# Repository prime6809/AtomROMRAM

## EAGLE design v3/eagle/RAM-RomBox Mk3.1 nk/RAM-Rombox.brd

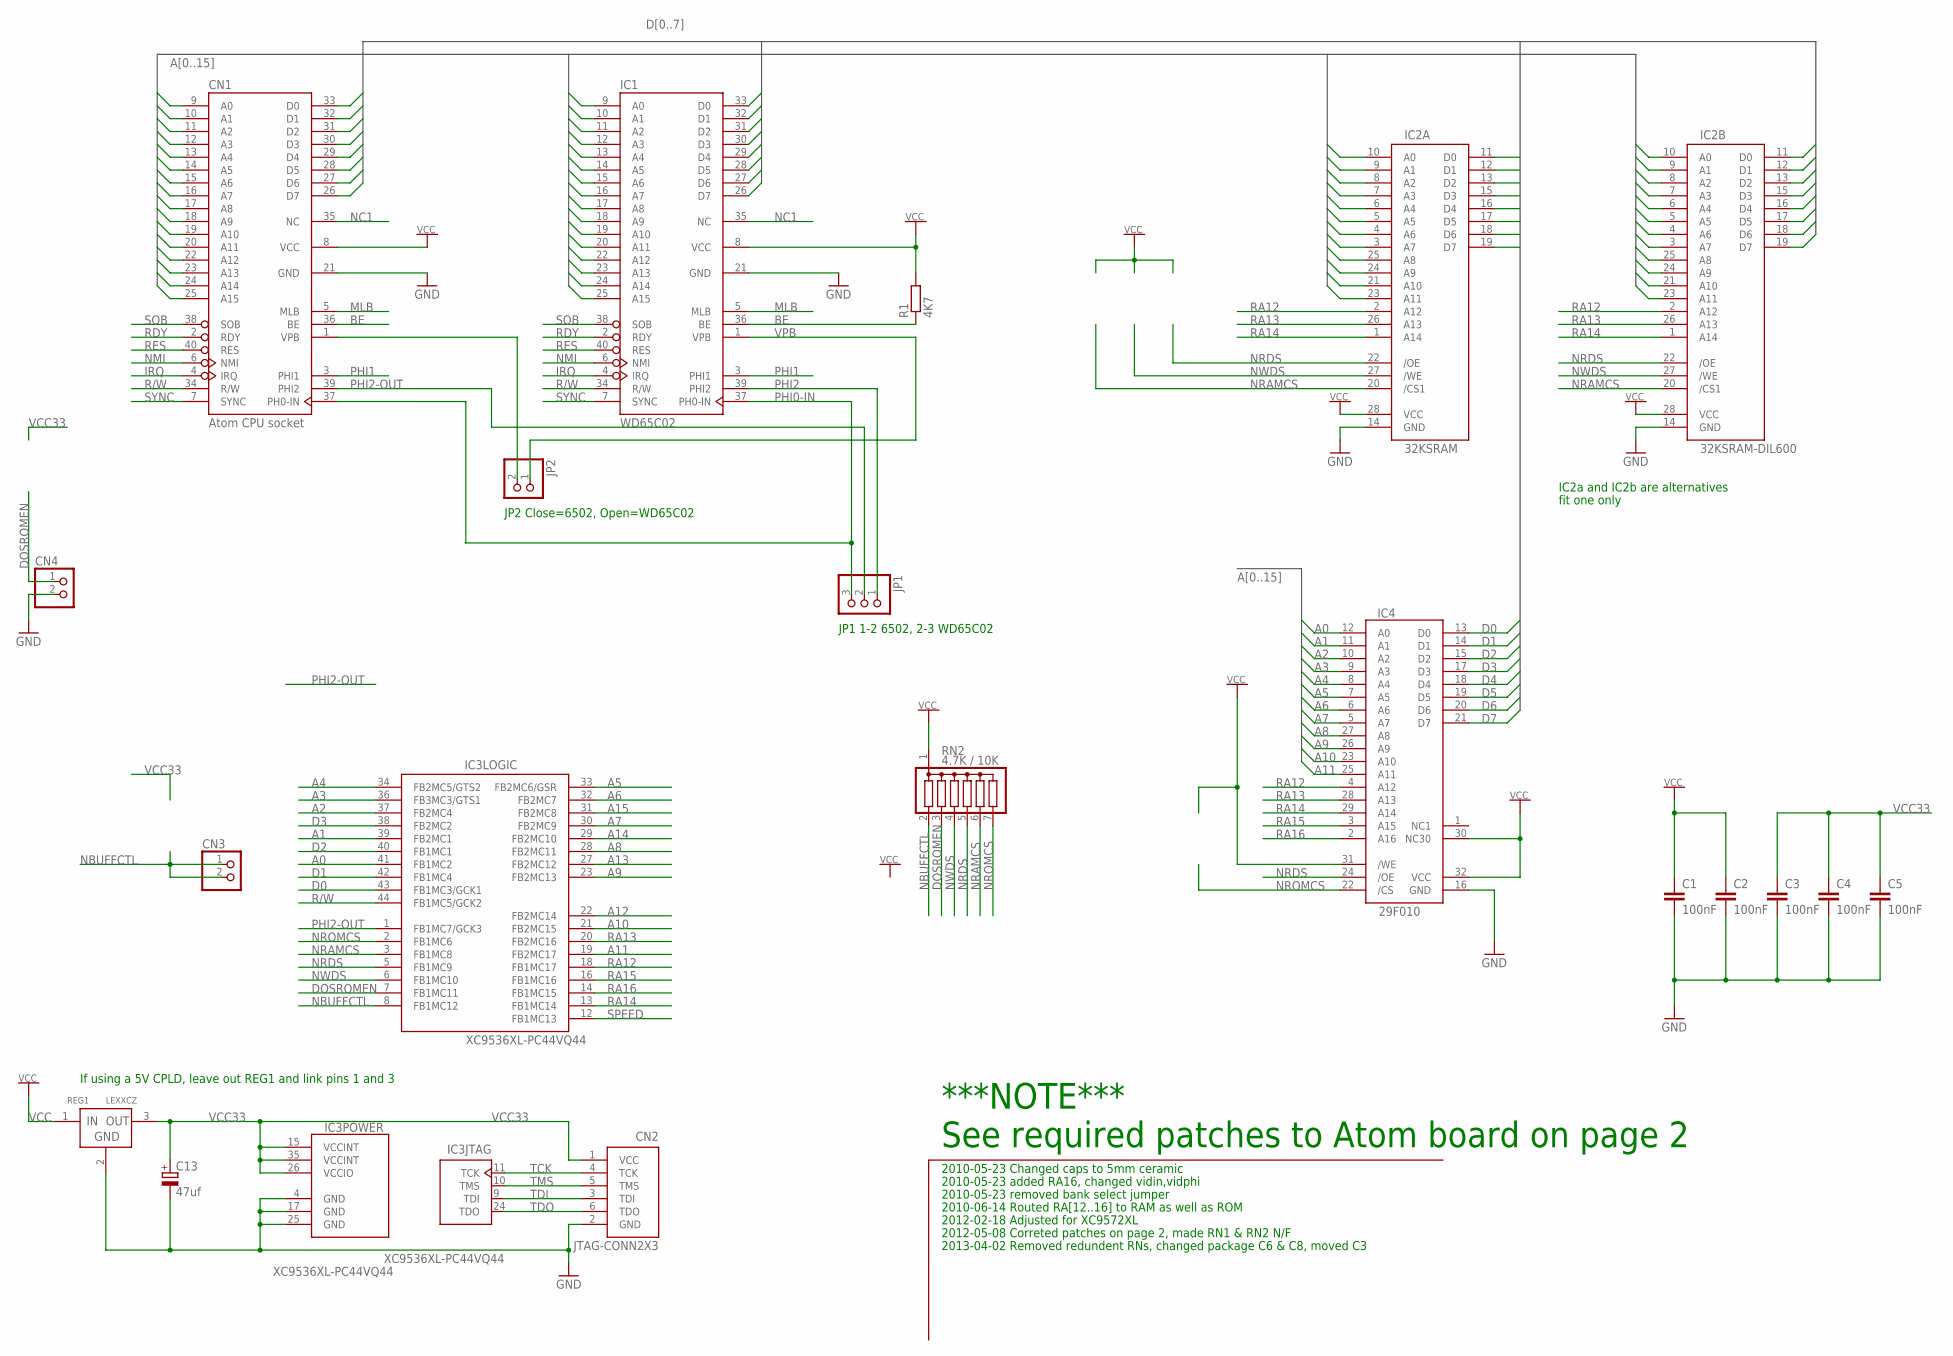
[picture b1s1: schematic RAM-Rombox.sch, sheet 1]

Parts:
C1, C2, C3: 100nF; C025-025X050
C4, C5: 100nF; C050-024X044
C13: 47uf; TAP5-45
CN1: Atom CPU socket; DIL40
CN2: JTAG-CONN2X3; 2X3
CN3, CN4: PINHD-1X2; 1X02
IC1: WD65C02; DIL40
IC2A: 32KSRAM; DIL28-3
IC2B: 32KSRAM-DIL600; DIL28-6
IC3: XC9536XL-PC44VQ44; SQFP-S-10X10-44
IC4: 29F010; DIL32
JP1: PINHD-1X3; 1X03
JP2: PINHD-1X2; 1X02
R1: 4K7; 0207/10
REG1: LEXXCZ; TO92-
RN2: 4.7K / 10K; SIL7

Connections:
A0: CN1.9 (A0), IC1.9 (A0), IC2A.10 (A0), IC2B.10 (A0), IC3.41 (FB1MC2), IC4.12 (A0)
A1: CN1.10 (A1), IC1.10 (A1), IC2A.9 (A1), IC2B.9 (A1), IC3.39 (FB2MC1), IC4.11 (A1)
A2: CN1.11 (A2), IC1.11 (A2), IC2A.8 (A2), IC2B.8 (A2), IC3.37 (FB2MC4), IC4.10 (A2)
A3: CN1.12 (A3), IC1.12 (A3), IC2A.7 (A3), IC2B.7 (A3), IC3.36 (FB3MC3/GTS1), IC4.9 (A3)
A4: CN1.13 (A4), IC1.13 (A4), IC2A.6 (A4), IC2B.6 (A4), IC3.34 (FB2MC5/GTS2), IC4.8 (A4)
A5: CN1.14 (A5), IC1.14 (A5), IC2A.5 (A5), IC2B.5 (A5), IC3.33 (FB2MC6/GSR), IC4.7 (A5)
A6: CN1.15 (A6), IC1.15 (A6), IC2A.4 (A6), IC2B.4 (A6), IC3.32 (FB2MC7), IC4.6 (A6)
A7: CN1.16 (A7), IC1.16 (A7), IC2A.3 (A7), IC2B.3 (A7), IC3.30 (FB2MC9), IC4.5 (A7)
A8: CN1.17 (A8), IC1.17 (A8), IC2A.25 (A8), IC2B.25 (A8), IC3.28 (FB2MC11), IC4.27 (A8)
A9: CN1.18 (A9), IC1.18 (A9), IC2A.24 (A9), IC2B.24 (A9), IC3.23 (FB2MC13), IC4.26 (A9)
A10: CN1.19 (A10), IC1.19 (A10), IC2A.21 (A10), IC2B.21 (A10), IC3.21 (FB2MC15), IC4.23 (A10)
A11: CN1.20 (A11), IC1.20 (A11), IC2A.23 (A11), IC2B.23 (A11), IC3.19 (FB2MC17), IC4.25 (A11)
A12: CN1.22 (A12), IC1.22 (A12), IC3.22 (FB2MC14)
A13: CN1.23 (A13), IC1.23 (A13), IC3.27 (FB2MC12)
A14: CN1.24 (A14), IC1.24 (A14), IC3.29 (FB2MC10)
A15: CN1.25 (A15), IC1.25 (A15), IC3.31 (FB2MC8)
BE: CN1.36 (BE), IC1.36 (BE), R1.1
D0: CN1.33 (D0), IC1.33 (D0), IC2A.11 (D0), IC2B.11 (D0), IC3.43 (FB1MC3/GCK1), IC4.13 (D0)
D1: CN1.32 (D1), IC1.32 (D1), IC2A.12 (D1), IC2B.12 (D1), IC3.42 (FB1MC4), IC4.14 (D1)
D2: CN1.31 (D2), IC1.31 (D2), IC2A.13 (D2), IC2B.13 (D2), IC3.40 (FB1MC1), IC4.15 (D2)
D3: CN1.30 (D3), IC1.30 (D3), IC2A.15 (D3), IC2B.15 (D3), IC3.38 (FB2MC2), IC4.17 (D3)
D4: CN1.29 (D4), IC1.29 (D4), IC2A.16 (D4), IC2B.16 (D4), IC4.18 (D4)
D5: CN1.28 (D5), IC1.28 (D5), IC2A.17 (D5), IC2B.17 (D5), IC4.19 (D5)
D6: CN1.27 (D6), IC1.27 (D6), IC2A.18 (D6), IC2B.18 (D6), IC4.20 (D6)
D7: CN1.26 (D7), IC1.26 (D7), IC2A.19 (D7), IC2B.19 (D7), IC4.21 (D7)
DOSROMEN: CN4.1, IC3.7 (FB1MC11), RN2.3
GND: C1.2, C2.2, C3.2, C4.2, C5.2, C13.-, CN1.21 (GND), CN2.2 (GND), CN4.2, IC1.21 (GND), IC2A.14 (GND), IC2B.14 (GND), IC3.4 (GND), IC3.17 (GND), IC3.25 (GND), IC4.16 (GND), REG1.2 (GND); also elsewhere on the board
IRQ: CN1.4 (IRQ), IC1.4 (IRQ)
MLB: CN1.5 (MLB), IC1.5 (MLB)
unnamed: CN1.1 (VPB), JP2.2
NBUFFCTL: CN3.1, CN3.2, IC3.8 (FB1MC12), RN2.2
NC1: CN1.35 (NC), IC1.35 (NC)
NMI: CN1.6 (NMI), IC1.6 (NMI)
NRAMCS: IC2A.20 (/CS1), IC2B.20 (/CS1), IC3.3 (FB1MC8), RN2.6
NRDS: IC2A.22 (/OE), IC2B.22 (/OE), IC3.5 (FB1MC9), IC4.24 (/OE), RN2.5
NROMCS: IC3.2 (FB1MC6), IC4.22 (/CS), RN2.7
NWDS: IC2A.27 (/WE), IC2B.27 (/WE), IC3.6 (FB1MC10), RN2.4
PHI0-IN: CN1.37 (PH0-IN), IC1.37 (PH0-IN), JP1.3
PHI1: CN1.3 (PHI1), IC1.3 (PHI1)
PHI2: IC1.39 (PHI2), JP1.1
PHI2-OUT: CN1.39 (PHI2), IC3.1 (FB1MC7/GCK3), JP1.2
R/W: CN1.34 (R/W), IC1.34 (R/W), IC3.44 (FB1MC5/GCK2)
RA12: IC2A.2 (A12), IC2B.2 (A12), IC3.18 (FB1MC17), IC4.4 (A12)
RA13: IC2A.26 (A13), IC2B.26 (A13), IC3.20 (FB2MC16), IC4.28 (A13)
RA14: IC2A.1 (A14), IC2B.1 (A14), IC3.13 (FB1MC14), IC4.29 (A14)
RA15: IC3.16 (FB1MC16), IC4.3 (A15)
RA16: IC3.14 (FB1MC15), IC4.2 (A16)
RDY: CN1.2 (RDY), IC1.2 (RDY)
RES: CN1.40 (RES), IC1.40 (RES)
SOB: CN1.38 (SOB), IC1.38 (SOB)
SPEED: IC3.12 (FB1MC13); also elsewhere on the board
SYNC: CN1.7 (SYNC), IC1.7 (SYNC)
TCK: CN2.4 (TCK), IC3.11 (TCK)
TDI: CN2.3 (TDI), IC3.9 (TDI)
TDO: CN2.6 (TDO), IC3.24 (TDO)
TMS: CN2.5 (TMS), IC3.10 (TMS)
VCC: C1.1, C2.1, CN1.8 (VCC), IC1.8 (VCC), IC2A.28 (VCC), IC2B.28 (VCC), IC4.30 (NC30), IC4.31 (/WE), IC4.32 (VCC), R1.2, REG1.1 (IN), RN2.1; also elsewhere on the board
VCC33: C3.1, C4.1, C5.1, C13.+, CN2.1 (VCC), IC3.15 (VCCINT), IC3.26 (VCCIO), IC3.35 (VCCINT), REG1.3 (OUT)
VPB: IC1.1 (VPB), JP2.1

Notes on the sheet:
JP1 1-2 6502, 2-3 WD65C02
JP2 Close=6502, Open=WD65C02
IC2a and IC2b are alternatives
fit one only
2010-05-23 Changed caps to 5mm ceramic
2010-05-23 added RA16, changed vidin,vidphi
2010-05-23 removed bank select jumper
2010-06-14 Routed RA[12..16] to RAM as well as ROM
2012-02-18 Adjusted for XC9572XL
If using a 5V CPLD, leave out REG1 and link pins 1 and 3
2012-05-08 Correted patches on page 2, made RN1 & RN2 N/F
***NOTE***
See required patches to Atom board on page 2
2013-04-02 Removed redundent RNs, changed package C6 & C8, moved C3

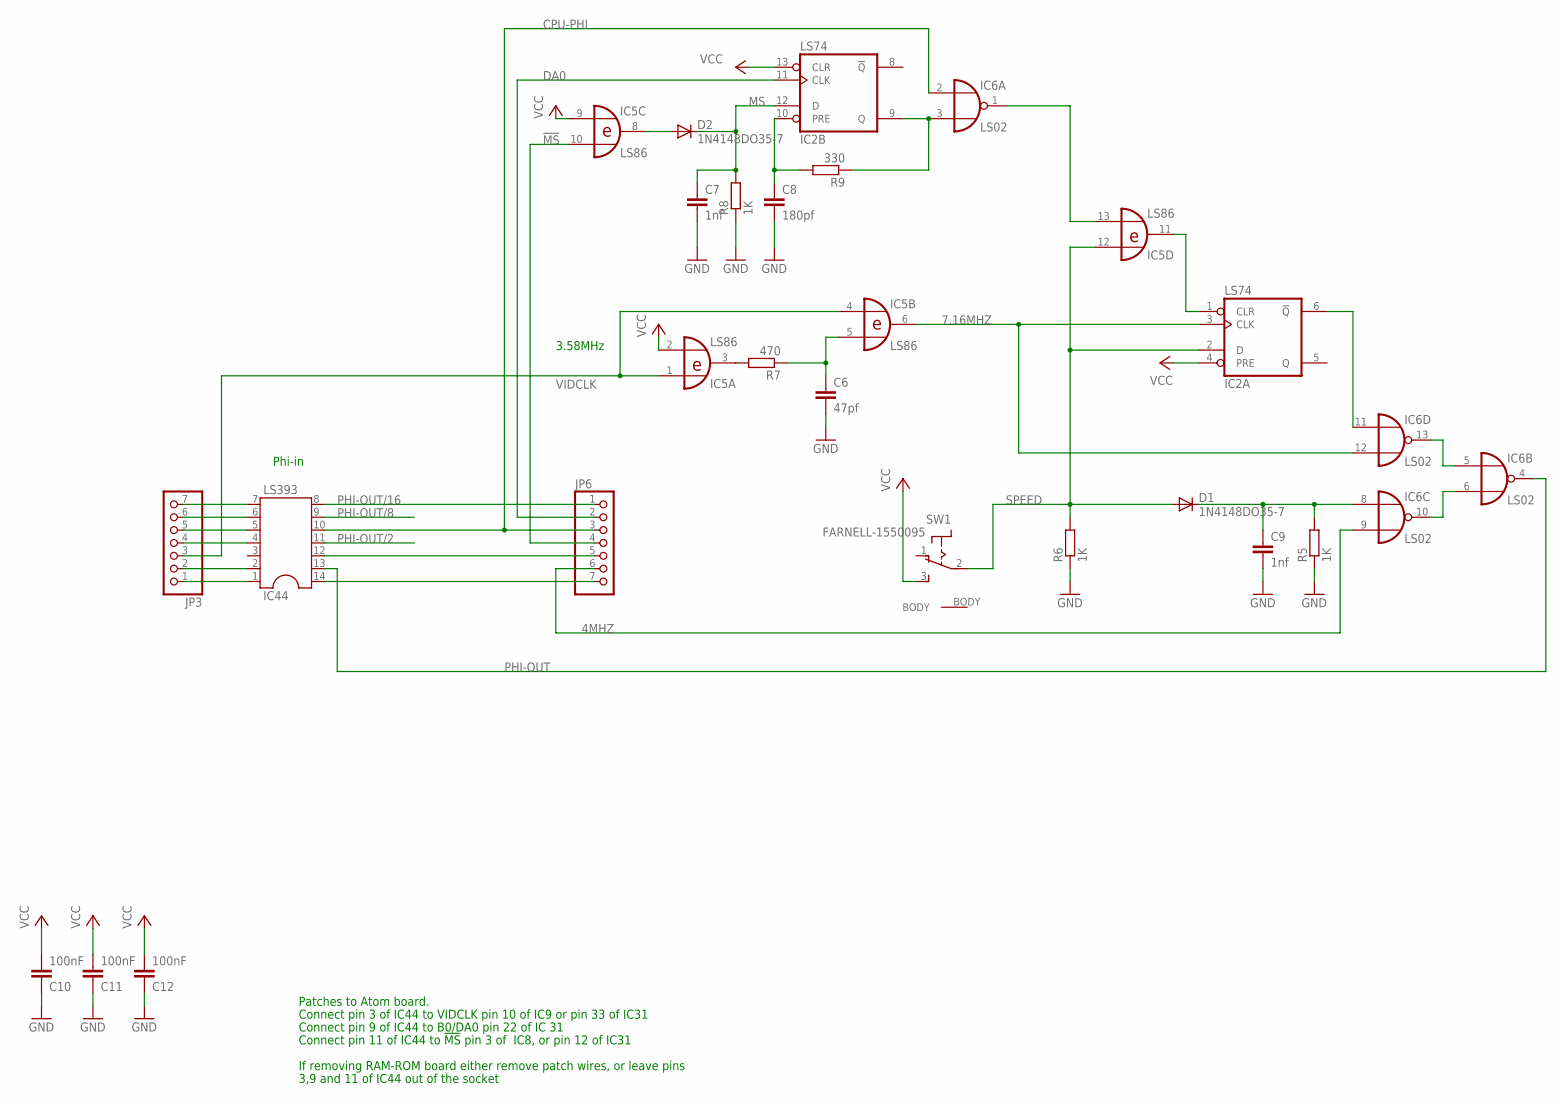
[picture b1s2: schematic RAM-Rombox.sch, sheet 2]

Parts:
C6: 47pf; C025-025X050
C7, C9: 1nf; C025-025X050
C8: 180pf; C025-025X050
C10, C11, C12: 100nF; C025-025X050
D1, D2: 1N4148DO35-7; DO35-7
IC2: LS74; DIL14
IC5: LS86; DIL14
IC6: LS02; DIL14
IC44: LS393; DIL14
JP3, JP6: PINHD-1X7; 1X07
R5, R6, R8: 1K; 0204/7
R7: 470; 0204/7
R9: 330; 0204/7
SW1: FARNELL-1550095; SPST-TOGGLE

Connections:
4MHZ: IC6.9 (I1), JP6.6
7.16MHZ: IC2.3 (CLK), IC5.6 (O), IC6.12 (I1)
!MS: IC5.10 (I1), JP6.4
CPU-PHI: IC6.2 (I0), IC44.10, JP6.3
DA0: IC2.11 (CLK), JP6.2
GND: C6.2, C7.2, C8.2, C9.2, C10.1, C11.1, C12.1, IC2.7 (GND), IC5.7 (GND), IC6.7 (GND), R5.1, R6.1, R8.1; also elsewhere on the board
MS: C7.1, D2.C, IC2.12 (D), R8.2
unnamed: C6.1, IC5.5 (I1), R7.1
unnamed: IC6.6 (I1), IC6.10 (O)
unnamed: IC6.5 (I0), IC6.13 (O)
unnamed: IC2.1 (CLR), IC5.11 (O)
unnamed: IC2.6 (!Q), IC6.11 (I0)
unnamed: IC5.3 (O), R7.2
unnamed: D2.A, IC5.8 (O)
unnamed: IC5.13 (I1), IC6.1 (O)
unnamed: IC2.9 (Q), IC6.3 (I1), R9.1
unnamed: C8.1, IC2.10 (PRE), R9.2
unnamed: IC44.6, JP3.6
unnamed: C9.1, D1.C, IC6.8 (I0), R5.2
unnamed: IC44.5, JP3.5
unnamed: IC44.4, JP3.4
unnamed: IC44.2, JP3.2
unnamed: IC44.1, JP3.1
unnamed: IC44.12, JP6.5
unnamed: IC44.14, JP6.7
unnamed: IC44.7, JP3.7
PHI-OUT: IC6.4 (O), IC44.13
PHI-OUT/2: IC44.11
PHI-OUT/8: IC44.9
PHI-OUT/16: IC44.8, JP6.1
SPEED: D1.A, IC2.2 (D), IC5.12 (I0), R6.2, SW1.2 (COMMON); also elsewhere on the board
VCC: C10.2, C11.2, C12.2, IC2.4 (PRE), IC2.13 (CLR), IC2.14 (VCC), IC5.2 (I1), IC5.9 (I0), IC5.14 (VCC), IC6.14 (VCC), SW1.3 (RIGHT); also elsewhere on the board
VIDCLK: IC5.1 (I0), IC5.4 (I0), JP3.3

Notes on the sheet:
3.58MHz
Phi-in
Patches to Atom board.
Connect pin 11 of IC44 to !MS! pin 3 of IC8, or pin 12 of IC31
Connect pin 3 of IC44 to VIDCLK pin 10 of IC9 or pin 33 of IC31
If removing RAM-ROM board either remove patch wires, or leave pins
3,9 and 11 of IC44 out of the socket
Connect pin 9 of IC44 to B0/DA0 pin 22 of IC 31

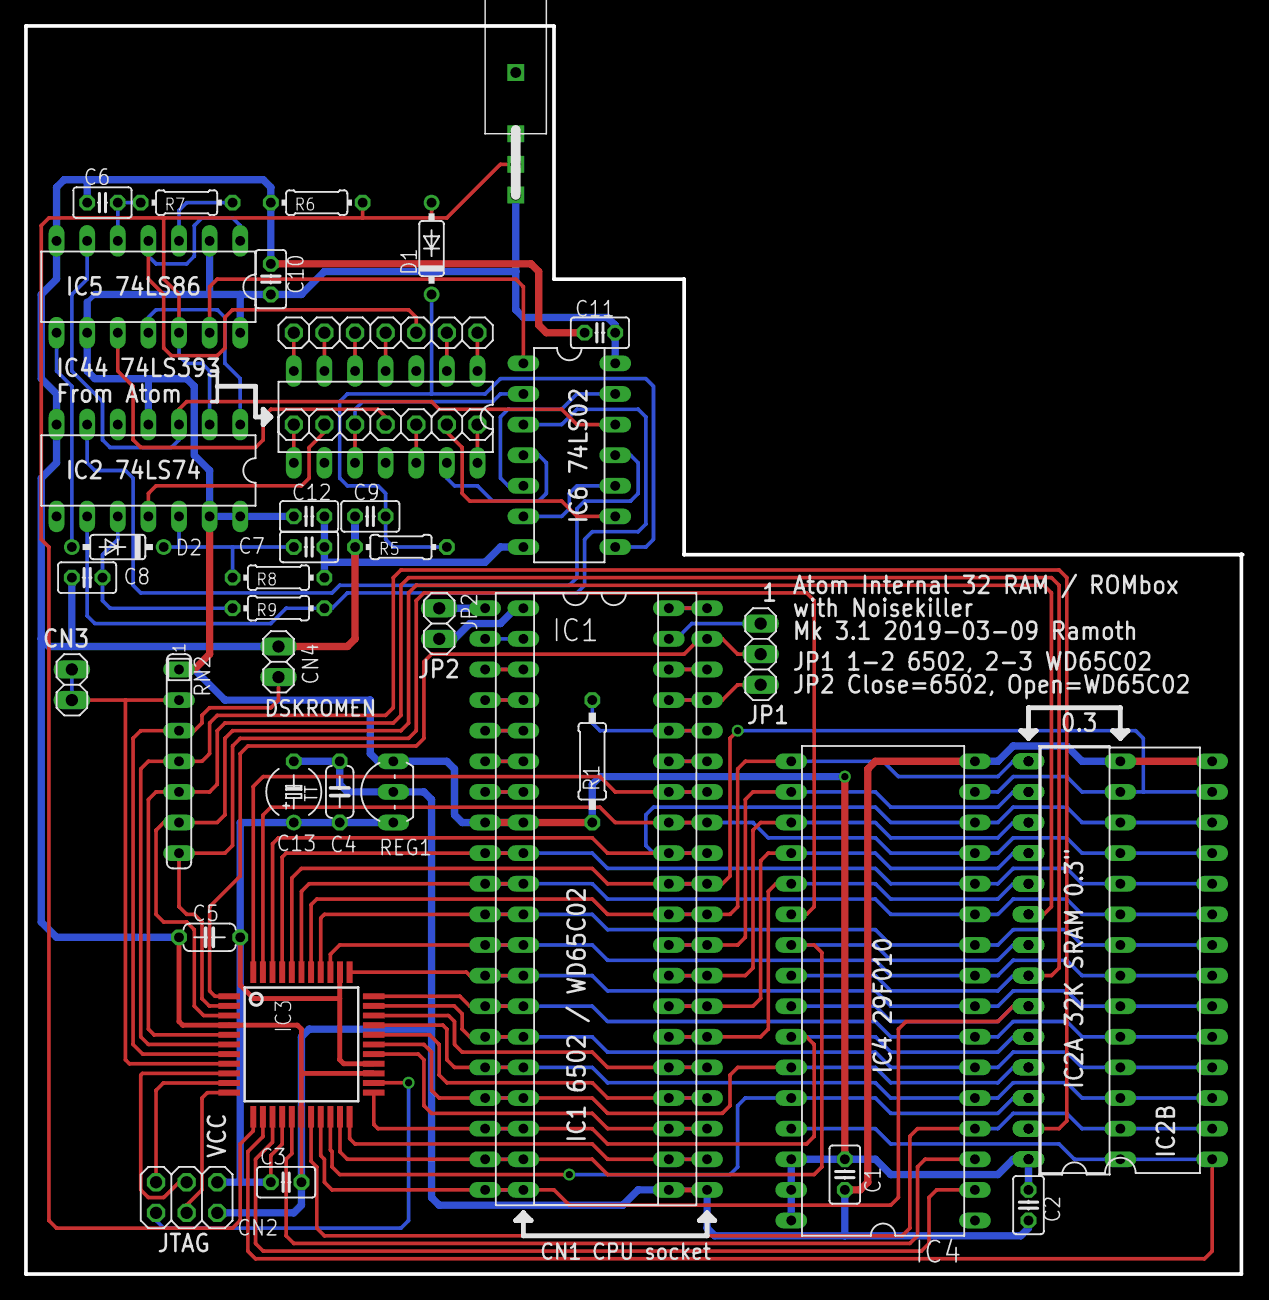
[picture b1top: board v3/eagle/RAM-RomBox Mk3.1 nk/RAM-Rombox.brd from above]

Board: 2 copper layers, 101.0 x 103.6 mm, 41 parts (0 on the bottom side), 87 nets.

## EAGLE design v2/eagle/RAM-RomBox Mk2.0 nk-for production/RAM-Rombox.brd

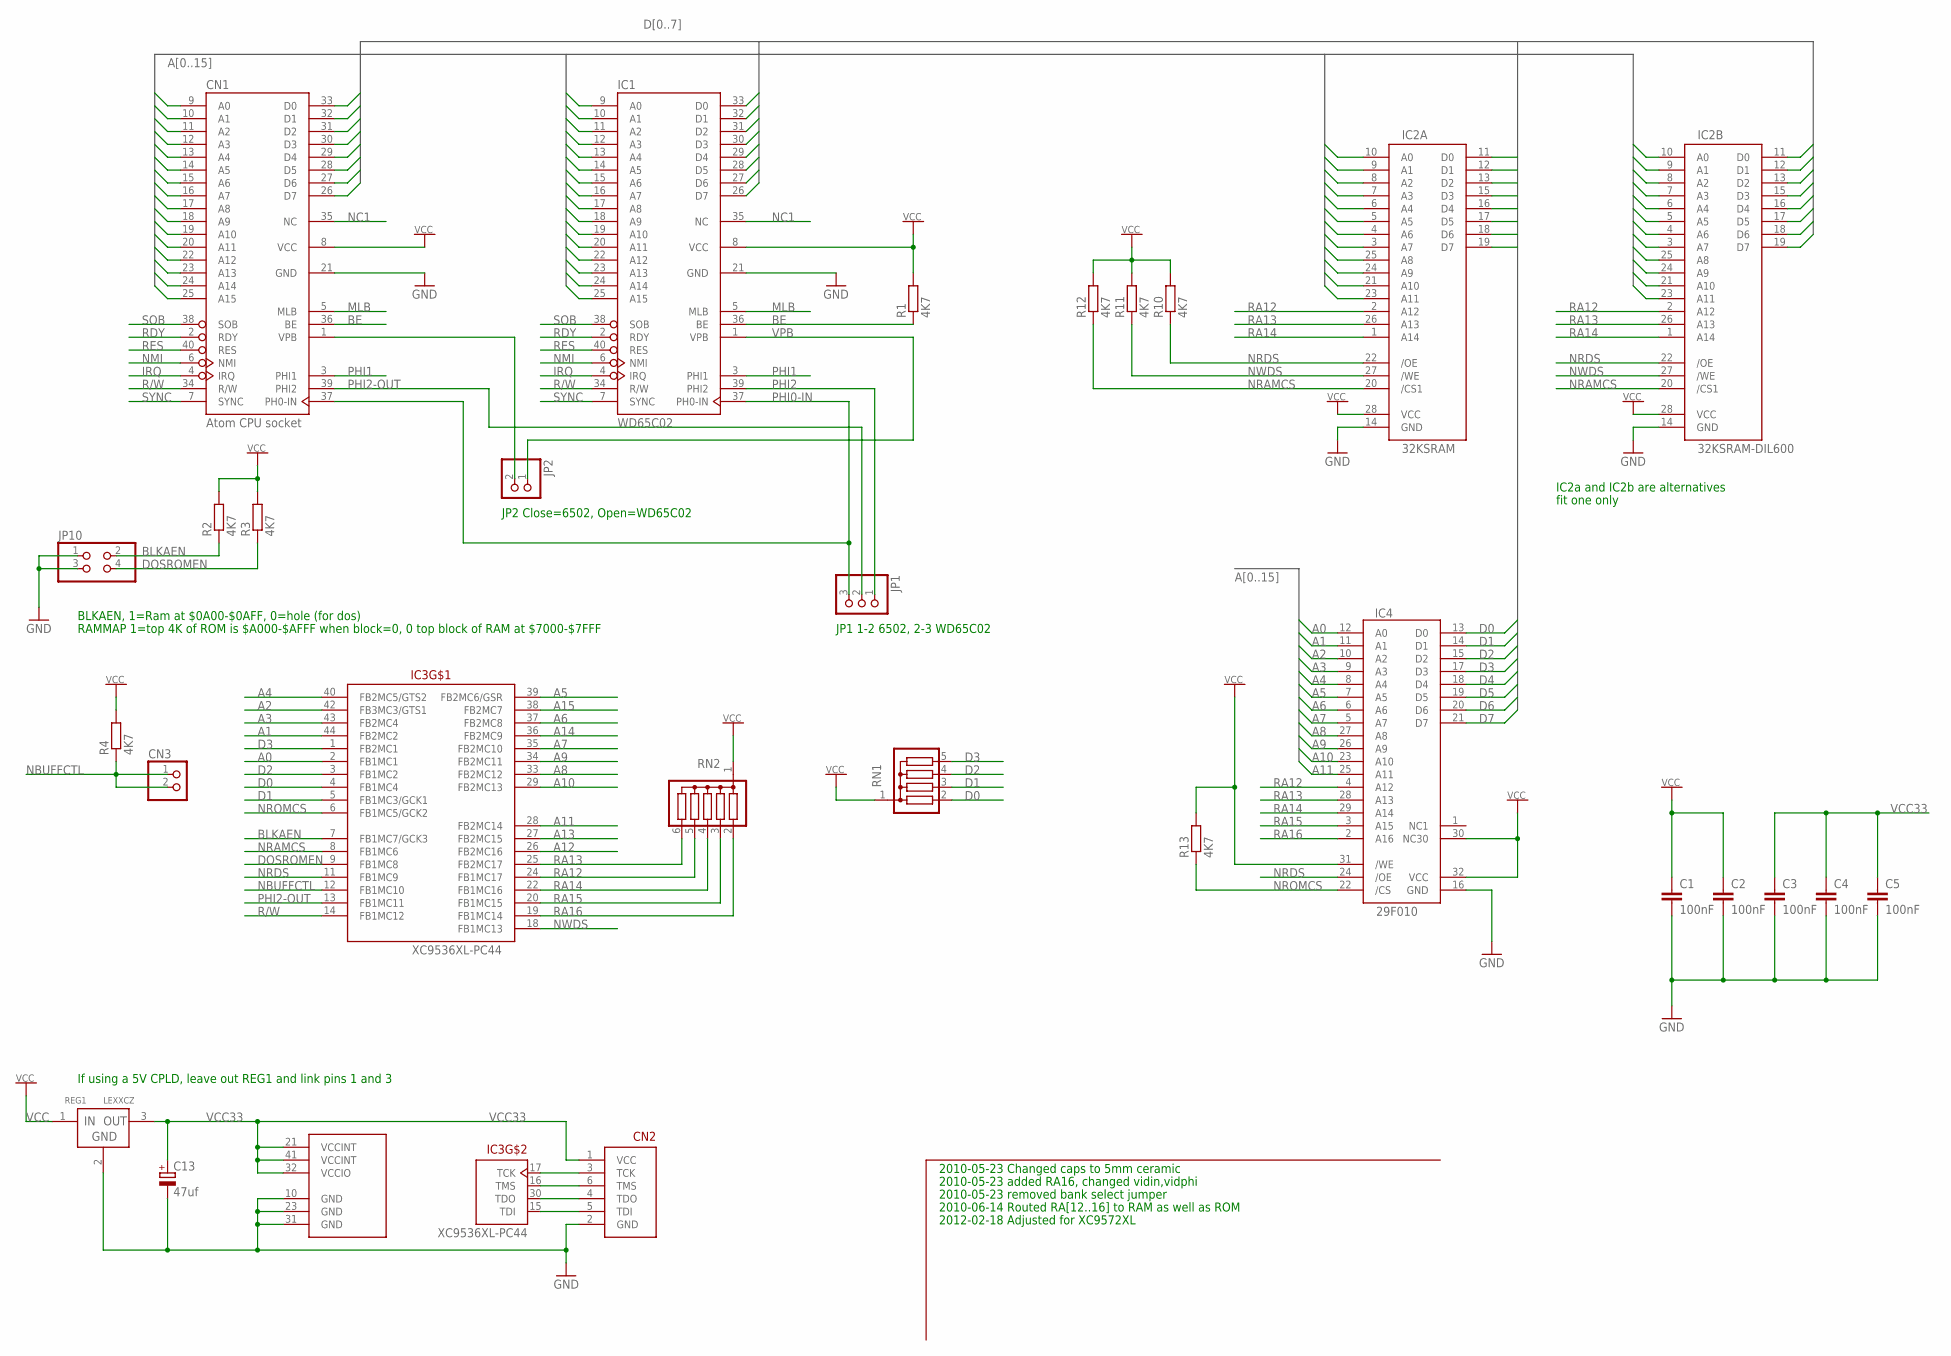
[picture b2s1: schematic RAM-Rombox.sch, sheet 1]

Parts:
C1, C2, C4, C5: 100nF; C050-024X044
C3: 100nF; C025-025X050
C13: 47uf; TAP5-45
CN1: Atom CPU socket; DIL40
CN2: JTAG-CONN; 1X06
CN3: PINHD-1X2; 1X02
IC1: WD65C02; DIL40
IC2A: 32KSRAM; DIL28-3
IC2B: 32KSRAM-DIL600; DIL28-6
IC3: XC9536XL-PC44; PLCC-S44
IC4: 29F010; DIL32
JP1: PINHD-1X3; 1X03
JP2: PINHD-1X2; 1X02
JP10: PINHD-2X2; 2X02
R1, R4, R10, R11, R12, R13: 4K7; 0207/10
R2, R3: 4K7; 0204V
REG1: LEXXCZ; TO92-
RN1: G04R; SIL5
RN2: G05R; SIL6

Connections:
A0: CN1.9 (A0), IC1.9 (A0), IC2A.10 (A0), IC2B.10 (A0), IC3.2 (FB1MC1), IC4.12 (A0)
A1: CN1.10 (A1), IC1.10 (A1), IC2A.9 (A1), IC2B.9 (A1), IC3.44 (FB2MC2), IC4.11 (A1)
A2: CN1.11 (A2), IC1.11 (A2), IC2A.8 (A2), IC2B.8 (A2), IC3.42 (FB3MC3/GTS1), IC4.10 (A2)
A3: CN1.12 (A3), IC1.12 (A3), IC2A.7 (A3), IC2B.7 (A3), IC3.43 (FB2MC4), IC4.9 (A3)
A4: CN1.13 (A4), IC1.13 (A4), IC2A.6 (A4), IC2B.6 (A4), IC3.40 (FB2MC5/GTS2), IC4.8 (A4)
A5: CN1.14 (A5), IC1.14 (A5), IC2A.5 (A5), IC2B.5 (A5), IC3.39 (FB2MC6/GSR), IC4.7 (A5)
A6: CN1.15 (A6), IC1.15 (A6), IC2A.4 (A6), IC2B.4 (A6), IC3.37 (FB2MC8), IC4.6 (A6)
A7: CN1.16 (A7), IC1.16 (A7), IC2A.3 (A7), IC2B.3 (A7), IC3.35 (FB2MC10), IC4.5 (A7)
A8: CN1.17 (A8), IC1.17 (A8), IC2A.25 (A8), IC2B.25 (A8), IC3.33 (FB2MC12), IC4.27 (A8)
A9: CN1.18 (A9), IC1.18 (A9), IC2A.24 (A9), IC2B.24 (A9), IC3.34 (FB2MC11), IC4.26 (A9)
A10: CN1.19 (A10), IC1.19 (A10), IC2A.21 (A10), IC2B.21 (A10), IC3.29 (FB2MC13), IC4.23 (A10)
A11: CN1.20 (A11), IC1.20 (A11), IC2A.23 (A11), IC2B.23 (A11), IC3.28 (FB2MC14), IC4.25 (A11)
A12: CN1.22 (A12), IC1.22 (A12), IC3.26 (FB2MC16)
A13: CN1.23 (A13), IC1.23 (A13), IC3.27 (FB2MC15)
A14: CN1.24 (A14), IC1.24 (A14), IC3.36 (FB2MC9)
A15: CN1.25 (A15), IC1.25 (A15), IC3.38 (FB2MC7)
BE: CN1.36 (BE), IC1.36 (BE), R1.1
BLKAEN: IC3.7 (FB1MC7/GCK3), JP10.2, R2.1
D0: CN1.33 (D0), IC1.33 (D0), IC2A.11 (D0), IC2B.11 (D0), IC3.4 (FB1MC4), IC4.13 (D0), RN1.2
D1: CN1.32 (D1), IC1.32 (D1), IC2A.12 (D1), IC2B.12 (D1), IC3.5 (FB1MC3/GCK1), IC4.14 (D1), RN1.3
D2: CN1.31 (D2), IC1.31 (D2), IC2A.13 (D2), IC2B.13 (D2), IC3.3 (FB1MC2), IC4.15 (D2), RN1.4
D3: CN1.30 (D3), IC1.30 (D3), IC2A.15 (D3), IC2B.15 (D3), IC3.1 (FB2MC1), IC4.17 (D3), RN1.5
D4: CN1.29 (D4), IC1.29 (D4), IC2A.16 (D4), IC2B.16 (D4), IC4.18 (D4)
D5: CN1.28 (D5), IC1.28 (D5), IC2A.17 (D5), IC2B.17 (D5), IC4.19 (D5)
D6: CN1.27 (D6), IC1.27 (D6), IC2A.18 (D6), IC2B.18 (D6), IC4.20 (D6)
D7: CN1.26 (D7), IC1.26 (D7), IC2A.19 (D7), IC2B.19 (D7), IC4.21 (D7)
DOSROMEN: IC3.9 (FB1MC8), JP10.4, R3.1
GND: C1.2, C2.2, C3.2, C4.2, C5.2, C13.-, CN1.21 (GND), CN2.2 (GND), IC1.21 (GND), IC2A.14 (GND), IC2B.14 (GND), IC3.10 (GND), IC3.23 (GND), IC3.31 (GND), IC4.16 (GND), JP10.1, JP10.3, REG1.2 (GND); also elsewhere on the board
IRQ: CN1.4 (IRQ), IC1.4 (IRQ)
MLB: CN1.5 (MLB), IC1.5 (MLB)
unnamed: CN1.1 (VPB), JP2.2
unnamed: CN2.3 (TCK), IC3.17 (TCK)
unnamed: CN2.6 (TMS), IC3.16 (TMS)
unnamed: CN2.4 (TDO), IC3.30 (TDO)
unnamed: CN2.5 (TDI), IC3.15 (TDI)
NBUFFCTL: CN3.1, CN3.2, IC3.12 (FB1MC10), R4.1
NC1: CN1.35 (NC), IC1.35 (NC)
NMI: CN1.6 (NMI), IC1.6 (NMI)
NRAMCS: IC2A.20 (/CS1), IC2B.20 (/CS1), IC3.8 (FB1MC6), R12.1
NRDS: IC2A.22 (/OE), IC2B.22 (/OE), IC3.11 (FB1MC9), IC4.24 (/OE), R10.1
NROMCS: IC3.6 (FB1MC5/GCK2), IC4.22 (/CS), R13.1
NWDS: IC2A.27 (/WE), IC2B.27 (/WE), IC3.18 (FB1MC13), R11.1
PHI0-IN: CN1.37 (PH0-IN), IC1.37 (PH0-IN), JP1.3
PHI1: CN1.3 (PHI1), IC1.3 (PHI1)
PHI2: IC1.39 (PHI2), JP1.1
PHI2-OUT: CN1.39 (PHI2), IC3.13 (FB1MC11), JP1.2
R/W: CN1.34 (R/W), IC1.34 (R/W), IC3.14 (FB1MC12)
RA12: IC2A.2 (A12), IC2B.2 (A12), IC3.24 (FB1MC17), IC4.4 (A12), RN2.5
RA13: IC2A.26 (A13), IC2B.26 (A13), IC3.25 (FB2MC17), IC4.28 (A13), RN2.6
RA14: IC2A.1 (A14), IC2B.1 (A14), IC3.22 (FB1MC16), IC4.29 (A14), RN2.4
RA15: IC3.20 (FB1MC15), IC4.3 (A15), RN2.3
RA16: IC3.19 (FB1MC14), IC4.2 (A16), RN2.2
RDY: CN1.2 (RDY), IC1.2 (RDY)
RES: CN1.40 (RES), IC1.40 (RES)
SOB: CN1.38 (SOB), IC1.38 (SOB)
SYNC: CN1.7 (SYNC), IC1.7 (SYNC)
VCC: C1.1, C2.1, CN1.8 (VCC), IC1.8 (VCC), IC2A.28 (VCC), IC2B.28 (VCC), IC4.30 (NC30), IC4.31 (/WE), IC4.32 (VCC), R1.2, R2.2, R3.2, R4.2, R10.2, R11.2, R12.2, R13.2, REG1.1 (IN), RN1.1, RN2.1; also elsewhere on the board
VCC33: C3.1, C4.1, C5.1, C13.+, CN2.1 (VCC), IC3.21 (VCCINT), IC3.32 (VCCIO), IC3.41 (VCCINT), REG1.3 (OUT)
VPB: IC1.1 (VPB), JP2.1

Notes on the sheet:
JP1 1-2 6502, 2-3 WD65C02
JP2 Close=6502, Open=WD65C02
IC2a and IC2b are alternatives
fit one only
2010-05-23 Changed caps to 5mm ceramic
2010-05-23 added RA16, changed vidin,vidphi
2010-05-23 removed bank select jumper
BLKAEN, 1=Ram at $0A00-$0AFF, 0=hole (for dos)
RAMMAP 1=top 4K of ROM is $A000-$AFFF when block=0, 0 top block of RAM at $7000-$7FFF
2010-06-14 Routed RA[12..16] to RAM as well as ROM
2012-02-18 Adjusted for XC9572XL
If using a 5V CPLD, leave out REG1 and link pins 1 and 3

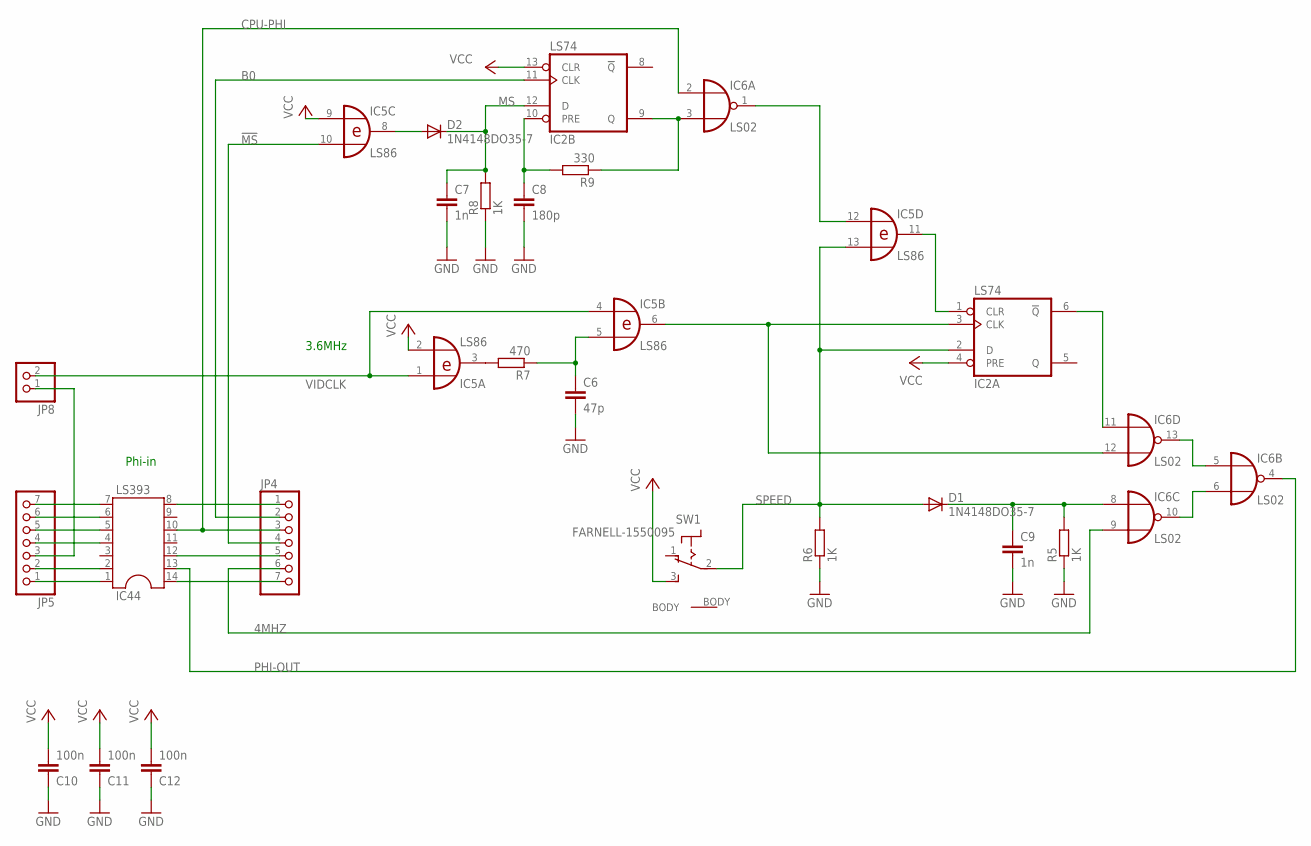
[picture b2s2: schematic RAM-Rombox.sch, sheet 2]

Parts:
C6: 47p; C050-024X044
C7, C9: 1n; C050-024X044
C8: 180p; C050-024X044
C10, C11, C12: 100n; C050-024X044
D1, D2: 1N4148DO35-7; DO35-7
IC2: LS74; DIL14
IC5: LS86; DIL14
IC6: LS02; DIL14
IC44: LS393; DIL14
JP4, JP5: PINHD-1X7; 1X07
JP8: PINHD-1X2; 1X02
R5, R6, R8: 1K; 0204/7
R7: 470; 0204/7
R9: 330; 0204/7
SW1: FARNELL-1550095; SPST-TOGGLE

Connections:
4MHZ: IC6.9 (I1), JP4.6
!MS: IC5.10 (I1), JP4.4
B0: IC2.11 (CLK), JP4.2
CPU-PHI: IC6.2 (I0), IC44.10, JP4.3
GND: C6.2, C7.2, C8.2, C9.2, C10.1, C11.1, C12.1, IC2.7 (GND), IC5.7 (GND), IC6.7 (GND), R5.1, R6.1, R8.1; also elsewhere on the board
MS: C7.1, D2.C, IC2.12 (D), R8.2
unnamed: C6.1, IC5.5 (I1), R7.1
unnamed: IC6.6 (I1), IC6.10 (O)
unnamed: IC6.5 (I0), IC6.13 (O)
unnamed: IC2.1 (CLR), IC5.11 (O)
unnamed: IC2.6 (!Q), IC6.11 (I0)
unnamed: IC5.3 (O), R7.2
unnamed: D2.A, IC5.8 (O)
unnamed: JP5.3, JP8.1
unnamed: IC5.12 (I0), IC6.1 (O)
unnamed: IC2.9 (Q), IC6.3 (I1), R9.1
unnamed: C8.1, IC2.10 (PRE), R9.2
unnamed: IC44.6, JP5.6
unnamed: C9.1, D1.C, IC6.8 (I0), R5.2
unnamed: IC44.5, JP5.5
unnamed: IC44.4, JP5.4
unnamed: IC44.2, JP5.2
unnamed: IC44.1, JP5.1
unnamed: IC44.8, JP4.1
unnamed: IC44.12, JP4.5
unnamed: IC44.14, JP4.7
unnamed: IC44.7, JP5.7
unnamed: IC2.3 (CLK), IC5.6 (O), IC6.12 (I1)
PHI-OUT: IC6.4 (O), IC44.13
SPEED: D1.A, IC2.2 (D), IC5.13 (I1), R6.2, SW1.2 (COMMON)
VCC: C10.2, C11.2, C12.2, IC2.4 (PRE), IC2.13 (CLR), IC2.14 (VCC), IC5.2 (I1), IC5.9 (I0), IC5.14 (VCC), IC6.14 (VCC), SW1.3 (RIGHT); also elsewhere on the board
VIDCLK: IC5.1 (I0), IC5.4 (I0), JP8.2

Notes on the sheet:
3.6MHz
Phi-in

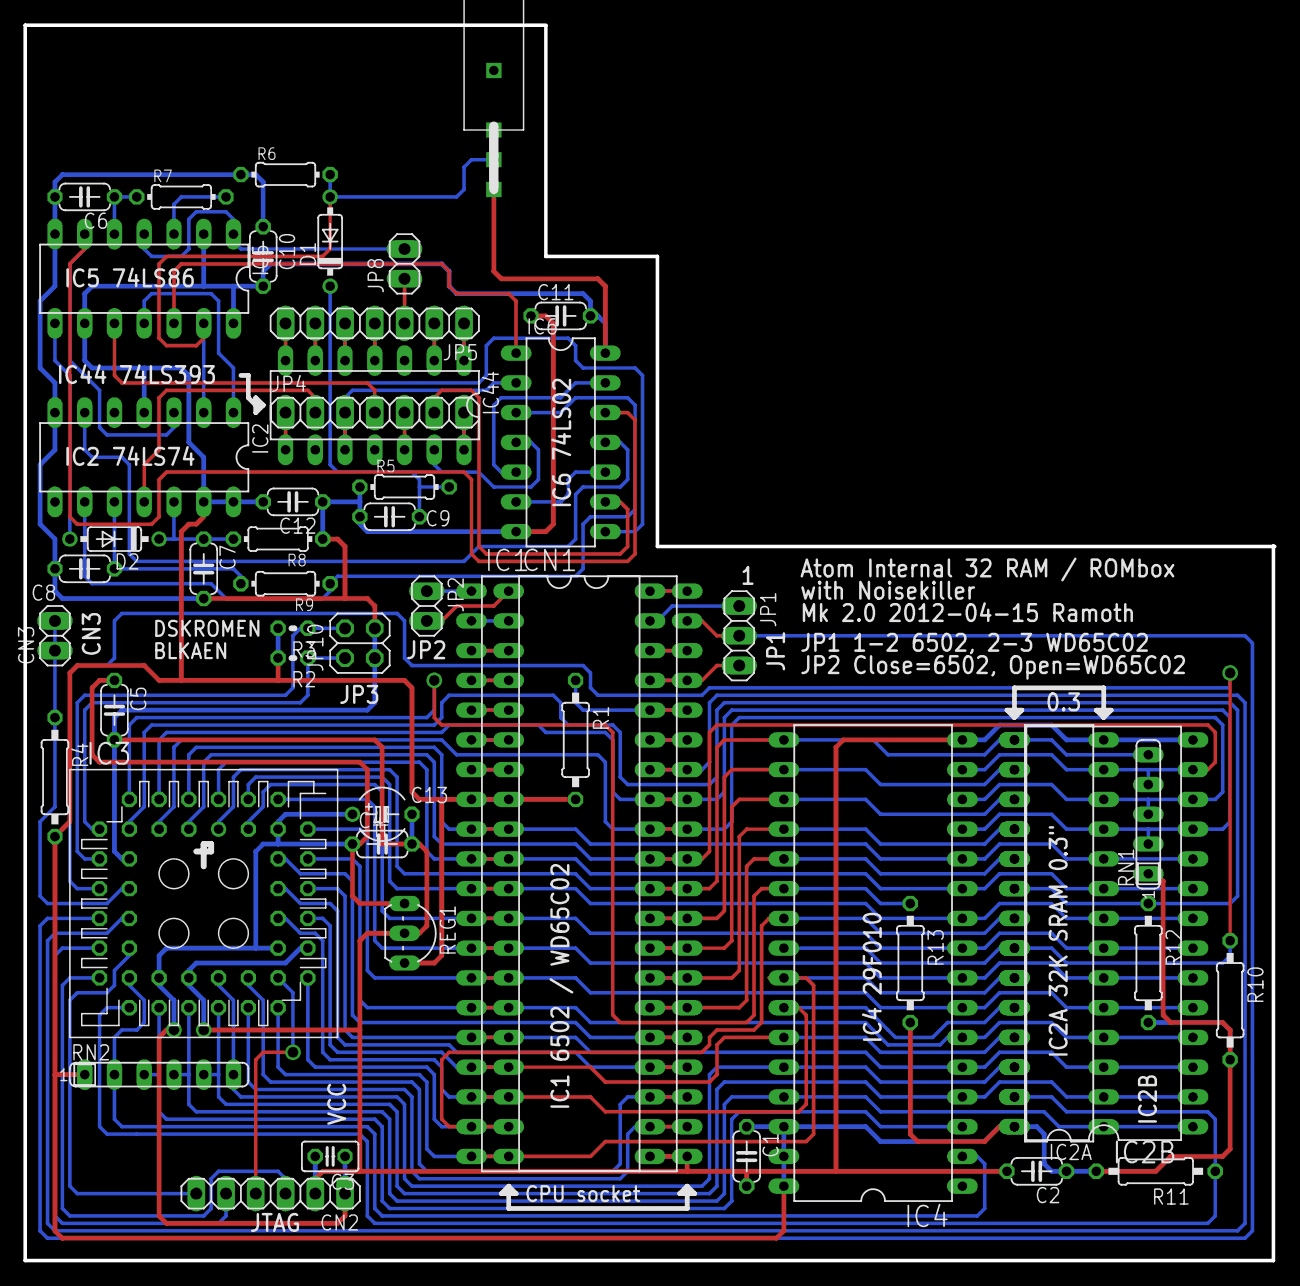
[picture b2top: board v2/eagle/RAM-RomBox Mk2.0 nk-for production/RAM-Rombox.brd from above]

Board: 2 copper layers, 106.7 x 105.5 mm, 50 parts (0 on the bottom side), 89 nets.

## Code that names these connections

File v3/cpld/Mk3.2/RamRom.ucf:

#PACE: Start of Constraints generated by PACE

#PACE: Start of PACE I/O Pin Assignments
NET "Addr<0>"  LOC = "p41"  ;
NET "Addr<10>"  LOC = "p21"  ;
NET "Addr<11>"  LOC = "p19"  ;
NET "Addr<12>"  LOC = "p22"  ;
NET "Addr<13>"  LOC = "p27"  ;
NET "Addr<14>"  LOC = "p29"  ;
NET "Addr<15>"  LOC = "p31"  ;
NET "Addr<1>"  LOC = "p39"  ;
NET "Addr<2>"  LOC = "p37"  ;
NET "Addr<3>"  LOC = "p36"  ;
NET "Addr<4>"  LOC = "p34"  ;
NET "Addr<5>"  LOC = "p33"  ;
NET "Addr<6>"  LOC = "p32"  ;
NET "Addr<7>"  LOC = "p30"  ;
NET "Addr<8>"  LOC = "p28"  ;
NET "Addr<9>"  LOC = "p23"  ;
NET "Data<0>"  LOC = "p43"  ;
NET "Data<1>"  LOC = "p42"  ;
NET "Data<2>"  LOC = "p40"  ;
NET "Data<3>"  LOC = "p38"  ;
NET "DskROMSW"  LOC = "p7"  ;
NET "NBuffCtl"  LOC = "p8"  ;
NET "NRAMCS"  LOC = "p3"  ;
NET "NRDS"  LOC = "p5"  ;
NET "NROMCS"  LOC = "p2"  ;
NET "NWDS"  LOC = "p6"  ;
NET "PHI2"  LOC = "p1"  ;
NET "RA<12>"  LOC = "p18"  ;
NET "RA<13>"  LOC = "p20"  ;
NET "RA<14>"  LOC = "p13"  ;
NET "RA<15>"  LOC = "p16"  ;
NET "RA<16>"  LOC = "p14"  ;
NET "RW"  LOC = "p44"  ;
NET "SpeedSW"  LOC = "p12"  ;

#PACE: Start of PACE Area Constraints

#PACE: Start of PACE Prohibit Constraints

#PACE: End of Constraints generated by PACE

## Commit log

2022-03-08 Initial commit of Atom RAMROM
